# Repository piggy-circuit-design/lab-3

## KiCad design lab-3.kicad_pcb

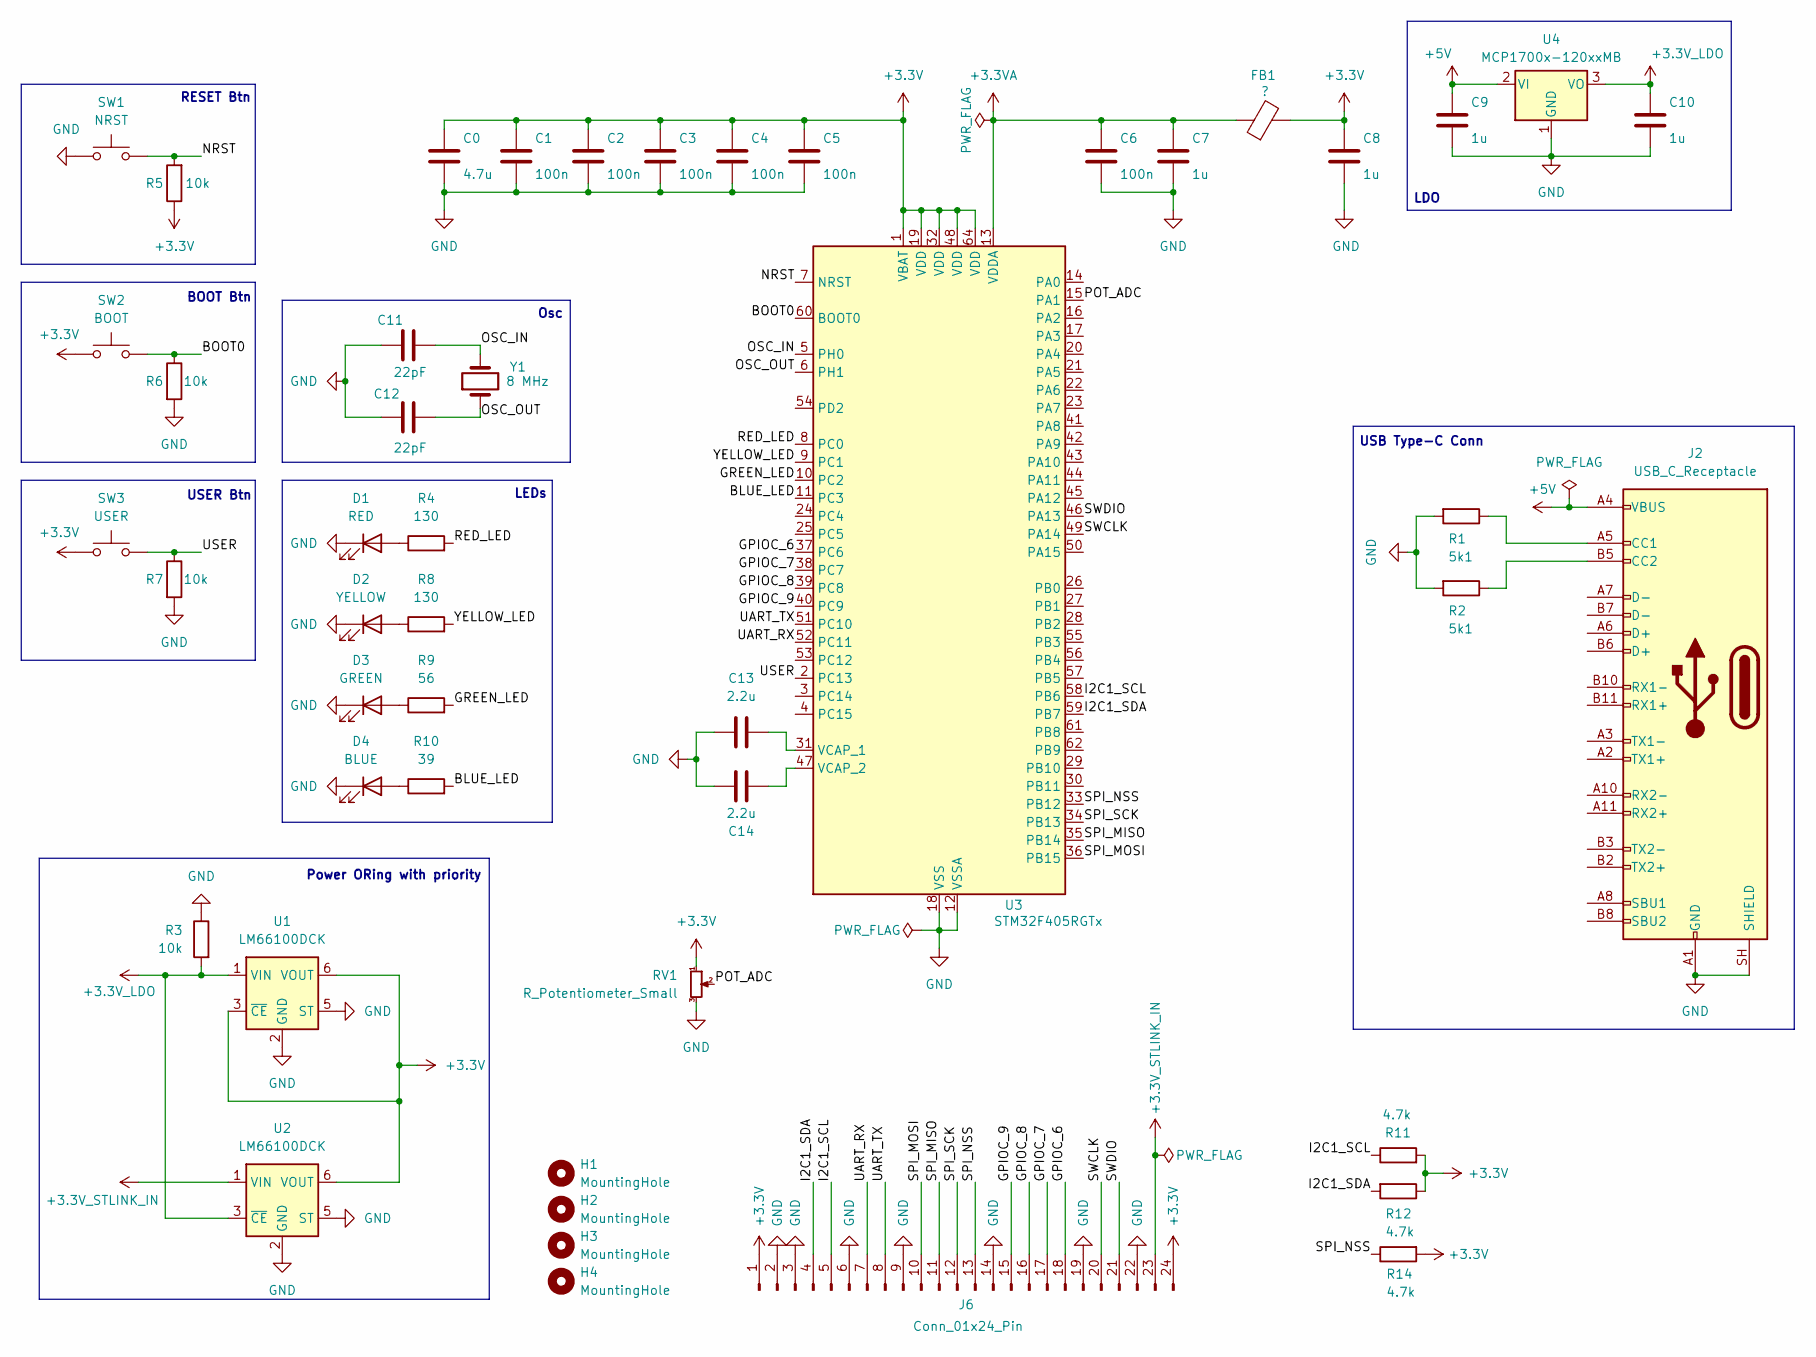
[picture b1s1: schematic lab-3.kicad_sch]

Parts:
C0: 4.7u; C_0603_1608Metric
C1, C2, C3, C4, C5, C6: 100n; C_0402_1005Metric
C7, C8, C9, C10: 1u; C_0603_1608Metric
C11, C12: 22pF; C_0402_1005Metric
C13, C14: 2.2u; C_0402_1005Metric
D1: RED; LED_0805_2012Metric
D2: YELLOW; LED_0805_2012Metric
D3: GREEN; LED_0805_2012Metric
D4: BLUE; LED_0805_2012Metric
FB1: ?; L_0603_1608Metric
H1, H2, H3, H4: MountingHole; MountingHole_2.2mm_M2_Pad
J2: USB_C_Receptacle; USB_C_Receptacle_Amphenol_12401610E4-2A
J6: Conn_01x24_Pin; PinHeader_1x24_P2.54mm_Vertical
R1, R2: 5k1; R_0603_1608Metric
R3: 10k; R_0603_1608Metric
R4, R8: 130; R_0402_1005Metric
R5, R6, R7: 10k; R_0402_1005Metric
R9: 56; R_0402_1005Metric
R10: 39; R_0402_1005Metric
R11, R12, R14: 4.7k; R_0402_1005Metric
RV1: R_Potentiometer_Small; Potentiometer_Bourns_3224G_Horizontal
SW1: NRST; SW_SPST_PTS647_Sx38
SW2: BOOT; SW_SPST_PTS647_Sx38
SW3: USER; SW_SPST_PTS647_Sx38
U1, U2: LM66100DCK; SOT-363_SC-70-6
U3: STM32F405RGTx; LQFP-64_10x10mm_P0.5mm
U4: MCP1700x-120xxMB; SOT-89-3
Y1: 8 MHz; Crystal_SMD_2520-4Pin_2.5x2.0mm

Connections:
+3.3V: C0.1, C1.1, C2.1, C3.1, C4.1, C5.1, C8.1, FB1.2, J6.1, J6.24, R5.1, R11.2, R12.1, R14.2, RV1.1, SW2.2, SW3.2, U1.3 (~CE), U1.6 (VOUT), U2.6 (VOUT), U3.1 (VBAT), U3.19 (VDD), U3.32 (VDD), U3.48 (VDD), U3.64 (VDD)
+3.3VA: C6.1, C7.1, FB1.1, U3.13 (VDDA)
+3.3V_LDO: C10.1, R3.2, U1.1 (VIN), U2.3 (~CE), U4.3 (VO)
+3.3V_STLINK_IN: J6.23, U2.1 (VIN)
+5V: C9.1, J2.A4 (VBUS), J2.A9 (VBUS), J2.B4 (VBUS), J2.B9 (VBUS), U4.2 (VI)
/BLUE_LED: R10.2, U3.11 (PC3)
/BOOT0: R6.1, SW2.1, U3.60 (BOOT0)
/GPIOC_6: J6.18, U3.37 (PC6)
/GPIOC_7: J6.17, U3.38 (PC7)
/GPIOC_8: J6.16, U3.39 (PC8)
/GPIOC_9: J6.15, U3.40 (PC9)
/GREEN_LED: R9.2, U3.10 (PC2)
/I2C1_SCL: J6.5, R11.1, U3.58 (PB6)
/I2C1_SDA: J6.4, R12.2, U3.59 (PB7)
/NRST: R5.2, SW1.1, U3.7 (NRST)
/OSC_IN: C11.2, U3.5 (PH0), Y1.2
/OSC_OUT: C12.2, U3.6 (PH1), Y1.1
/POT_ADC: RV1.2, U3.15 (PA1)
/RED_LED: R4.2, U3.8 (PC0)
/SPI_MISO: J6.11, U3.35 (PB14)
/SPI_MOSI: J6.10, U3.36 (PB15)
/SPI_NSS: J6.13, R14.1, U3.33 (PB12)
/SPI_SCK: J6.12, U3.34 (PB13)
/SWCLK: J6.20, U3.49 (PA14)
/SWDIO: J6.21, U3.46 (PA13)
/UART_RX: J6.7, U3.52 (PC11)
/UART_TX: J6.8, U3.51 (PC10)
/USER: R7.1, SW3.1, U3.2 (PC13)
/YELLOW_LED: R8.2, U3.9 (PC1)
GND: C0.2, C1.2, C2.2, C3.2, C4.2, C5.2, C6.2, C7.2, C8.2, C9.2, C10.2, C11.1, C12.1, C13.1, C14.2, D1.1 (K), D2.1 (K), D3.1 (K), D4.1 (K), J2.A1 (GND), J2.A12 (GND), J2.B1 (GND), J2.B12 (GND), J2.SH (SHIELD), J6.2, J6.3, J6.6, J6.9, J6.14, J6.19, J6.22, R1.2, R2.2, R3.1, R6.2, R7.2, RV1.3, SW1.2, U1.2 (GND), U1.5 (ST), U2.2 (GND), U2.5 (ST), U3.12 (VSSA), U3.18 (VSS), U3.63 (VSS), U4.1 (GND)
unnamed: D1.2 (A), R4.1
unnamed: D2.2 (A), R8.1
unnamed: D3.2 (A), R9.1
unnamed: D4.2 (A), R10.1
unnamed: J2.A5 (CC1), R1.1
unnamed: J2.B5 (CC2), R2.1
unnamed: C13.2, U3.31 (VCAP_1)
unnamed: C14.1, U3.47 (VCAP_2)

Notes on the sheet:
LEDs
BOOT Btn
Osc
USB Type-C Conn
Power ORing with priority
LDO
RESET Btn
USER Btn

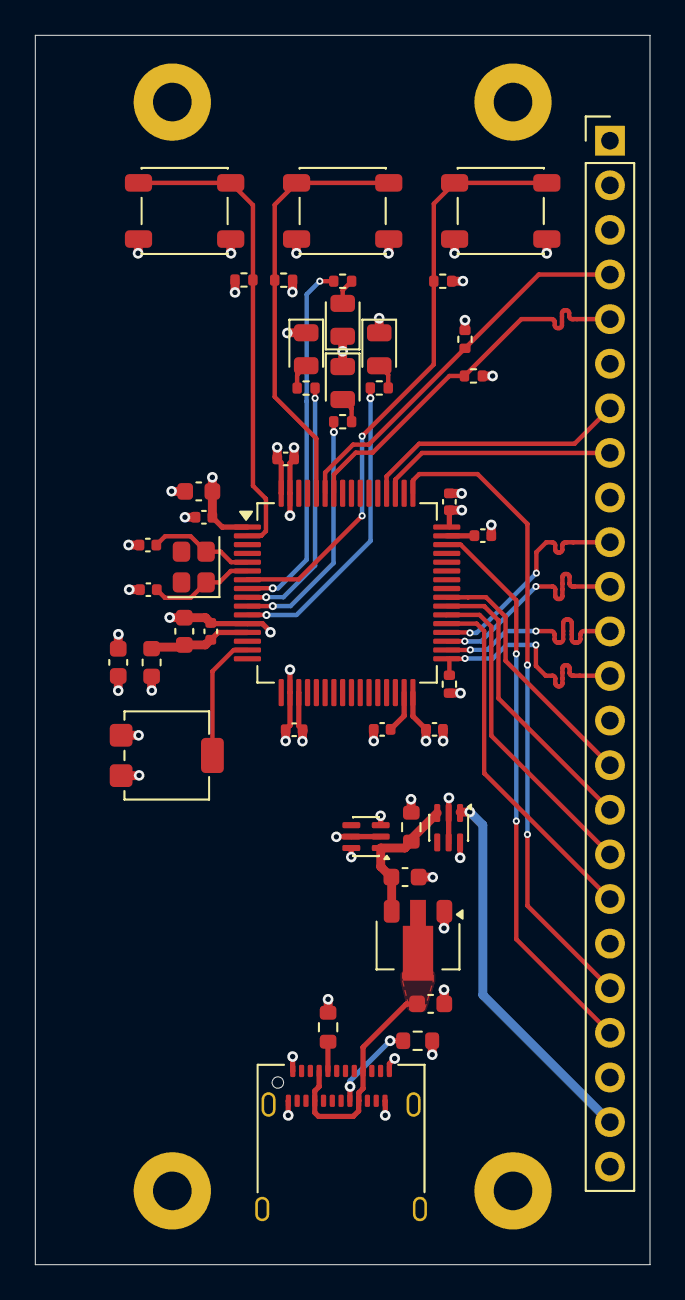
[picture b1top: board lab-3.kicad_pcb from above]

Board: 4 copper layers, 35.0 x 70.0 mm, 48 parts (0 on the bottom side), 38 nets.

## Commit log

2026-04-22 Init commit (lab-2 final result)
2026-04-22 Add I2C
2026-04-22 add single 1x24 pin header
2026-04-22 add uart and spi
2026-04-25 fix i2c and spi trace length
